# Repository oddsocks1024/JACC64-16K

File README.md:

# JACC64-16K

## Description
JACC64-16K: Just Another Commodore Cartridge.

A simple ROM cartridge for the Commodore 64 which takes a single 16K ROM image in an EPROM/EEPROM. Thanks to [World of Jani](https://blog.worldofjani.com/?p=879) for the original circuit design.

**Features**
* Power LED
* Reset Switch

## Bill of Materials

| Qty | Component                          |
|:---:|------------------------------------|
| 1   | 5mm LED                            |
| 1   | 6x6mm Tactile Push Button          |
| 1   | 330Ω Axial Resistor - ¼ watt (LED) |
| 1   | 10KΩ Axial Resistor - ¼ watt       |
| 2   | 1N4148 Diodes                      |
| 1   | 100nF Ceramic Capacitor            |
| 1   | M27C128 EPROM (or compatible)      |

* IC Sockets are optional.
* The LED resistor is nominally 330Ω but anything up to 1K is fine
* You will need to burn the 16K ROM image to the EPROM/EEPROM using a suitable programmer.
* Larger EPROMs/EEPROMs can be used but be sure to repeat the image to fill up the ROM.

## 3D Printable Case
A 3D printable case specifically designed for this PCB is also available. STLs are included in this repo.

* Insert the PCB into the base part of the case, making sure the holes in the PCB are aligned with the screw posts.
* Insert the reset pin into the top part of the case, then align it with the bottom part of the case.
* Use 2 x 3.5mm self-tapping screws to screw the case parts together. Max length about 15mm.

## Support Me
Everything is freely available so you can make your own PCB and case, however if you would like to support me, please see the following links.

* [My Projects](https://projects.amiga-hardware.com) - Donate on this page
* [Order the JACC64-16K PCB](https://www.pcbway.com/project/shareproject/JACC64_16K_C64_Cartridge_8e199b4f.html)
* [Order the JACC64-16K Case](https://www.pcbway.com/project/shareproject/JACC64_16K_C64_Cartridge_Case_78ec0fd1.html)

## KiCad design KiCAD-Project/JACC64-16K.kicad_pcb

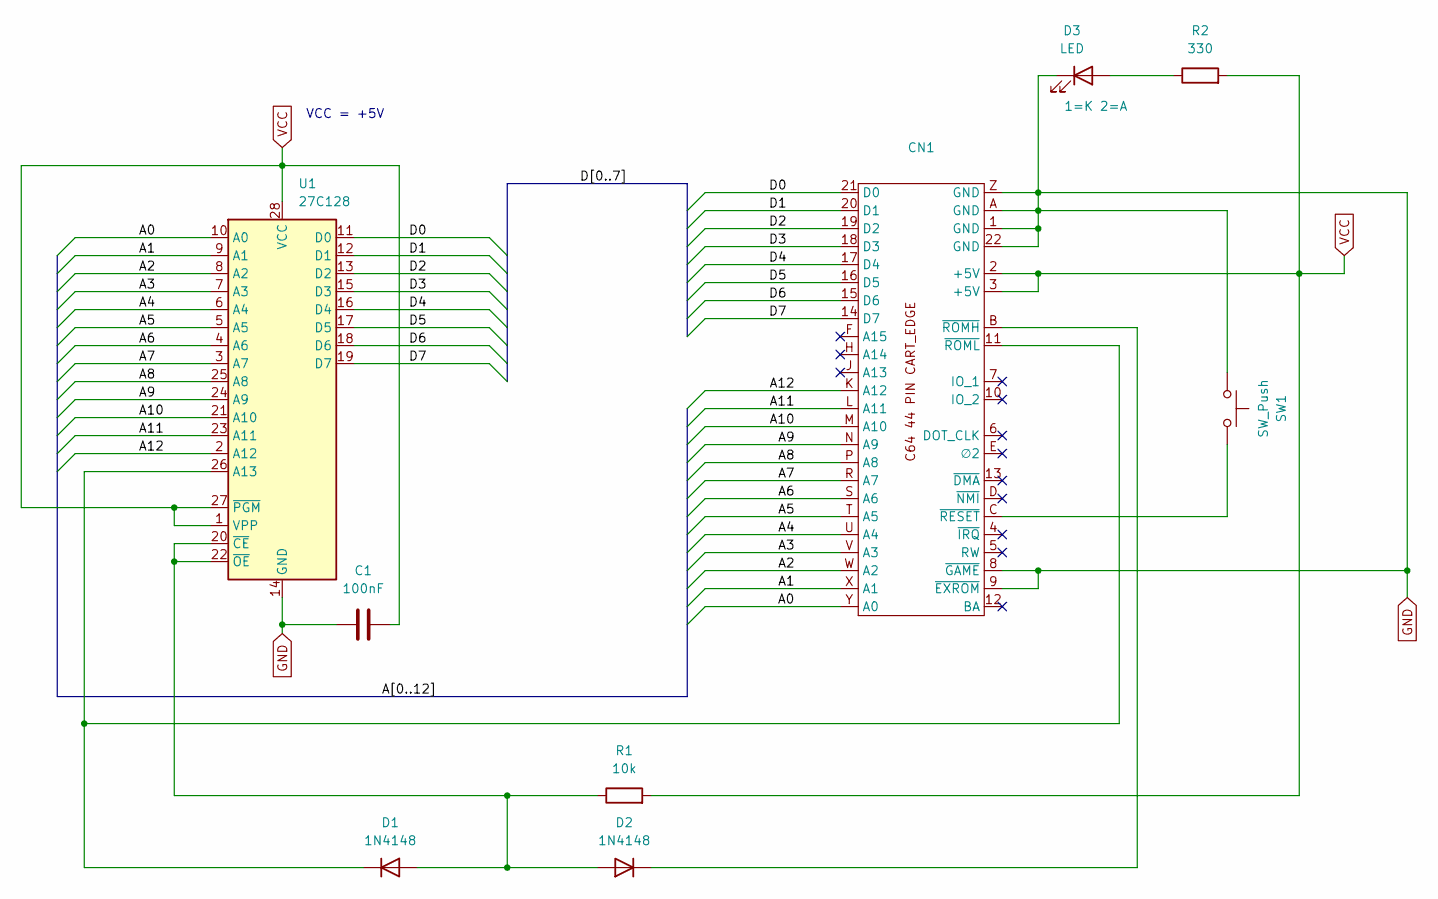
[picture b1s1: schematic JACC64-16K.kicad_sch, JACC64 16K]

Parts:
C1: 100nF; C_Disc_D3.0mm_W2.0mm_P2.50mm
CN1: C64 Expansion
D1, D2: 1N4148; D_DO-41_SOD81_P7.62mm_Horizontal
D3: LED; LED_D5.0mm
R1: 10k; R_Axial_DIN0207_L6.3mm_D2.5mm_P10.16mm_Horizontal
R2: 330; R_Axial_DIN0207_L6.3mm_D2.5mm_P10.16mm_Horizontal
SW1: SW_Push; SW_PUSH_6mm
U1: 27C128; DIP-28_W15.24mm

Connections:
/A0: CN1.Y (A0), U1.10 (A0)
/A1: CN1.X (A1), U1.9 (A1)
/A2: CN1.W (A2), U1.8 (A2)
/A3: CN1.V (A3), U1.7 (A3)
/A4: CN1.U (A4), U1.6 (A4)
/A5: CN1.T (A5), U1.5 (A5)
/A6: CN1.S (A6), U1.4 (A6)
/A7: CN1.R (A7), U1.3 (A7)
/A8: CN1.P (A8), U1.25 (A8)
/A9: CN1.N (A9), U1.24 (A9)
/A10: CN1.M (A10), U1.21 (A10)
/A11: CN1.L (A11), U1.23 (A11)
/A12: CN1.K (A12), U1.2 (A12)
/D0: CN1.21 (D0), U1.11 (D0)
/D1: CN1.20 (D1), U1.12 (D1)
/D2: CN1.19 (D2), U1.13 (D2)
/D3: CN1.18 (D3), U1.15 (D3)
/D4: CN1.17 (D4), U1.16 (D4)
/D5: CN1.16 (D5), U1.17 (D5)
/D6: CN1.15 (D6), U1.18 (D6)
/D7: CN1.14 (D7), U1.19 (D7)
GND: C1.1, CN1.1 (GND), CN1.8 (~GAME), CN1.9 (~EXROM), CN1.22 (GND), CN1.A (GND), CN1.Z (GND), D3.1 (K), SW1.1, U1.14 (GND)
unnamed: CN1.C (~RESET), SW1.2
unnamed: CN1.B (~ROMH), D2.1 (K)
unnamed: CN1.11 (~ROML), D1.1 (K), U1.26 (A13)
unnamed: D1.2 (A), D2.2 (A), R1.1, U1.20 (~CE), U1.22 (~OE)
unnamed: D3.2 (A), R2.1
VCC: C1.2, CN1.2 (+5V), CN1.3 (+5V), R1.2, R2.2, U1.1 (VPP), U1.27 (~PGM), U1.28 (VCC)

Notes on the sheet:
VCC = +5V

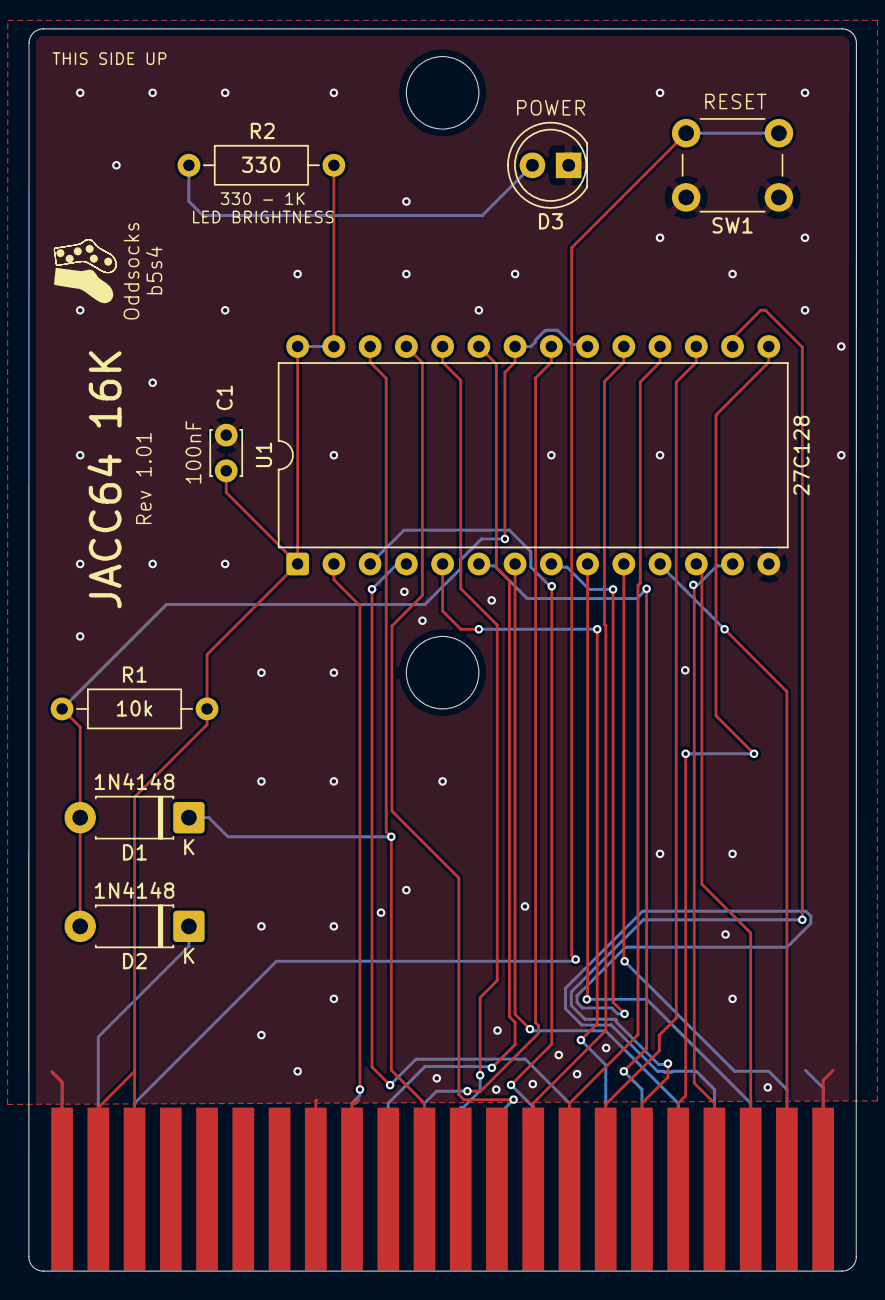
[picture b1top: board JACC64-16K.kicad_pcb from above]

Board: 2 copper layers, 58.0 x 87.1 mm, 9 parts (0 on the bottom side), 28 nets.

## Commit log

2025-11-09 Added gerbers and updated README.md
2025-11-30 Add license file
2025-11-30 Added PDF schematics
